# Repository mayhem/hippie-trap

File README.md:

# led-chandelier
LED bottle chandelier built for Nowhere 2015

by Robert Kaye and David Martin

Mock-up
=======

For a render of what we think this might look like a look in the design folder.

Hardware notes
==============

The chandalier made up of about 100 bottles that will have circuit boards with LEDs
inside them. 4 RGD LEDs (WS2812B) connected to an atmega128 will light up each bottle.
Communication happens over a bone simple serial connection, hopefully at 250kbps.
For serial timing and ram reasons, I chose the atmega128 over the attiny84.

The bottles will be connected to 5V power, ground and a communication line. The communication
will be via a line driver that broadcasts the serial signal to each bottle. The RPi can then
send either color information to each bottle or more interestingly send a crude set of instructions
on how to build a color animation. This way the chanelier can work in a centrally coordinated
mode or each bottle carrying out its own program.

.brd and .sch files for Eagle are in hardware folder.

Notes about the circuit
-----------------------

- Regulated 5V power supply in the body of the chandelier
- WS2812B LEDS: http://www.adafruit.com/datasheets/WS2812B.pdf
- MCU: atmega168
- Shottky diodes on the inputs.
- Program via a pogoplug, no actual connector will be on the board.

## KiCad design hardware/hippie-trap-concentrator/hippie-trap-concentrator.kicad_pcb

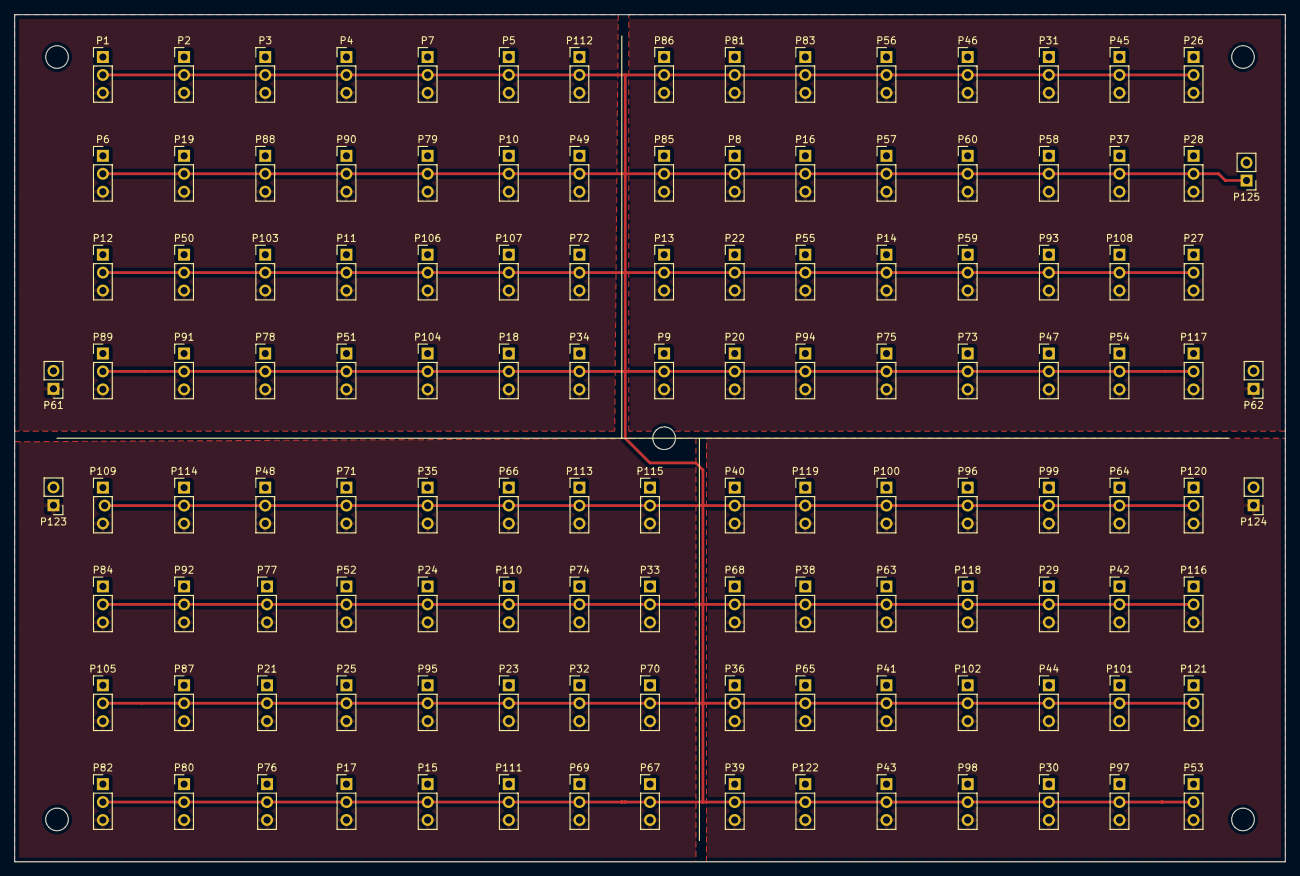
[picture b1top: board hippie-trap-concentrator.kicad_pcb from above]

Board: 2 copper layers, 180.0 x 120.0 mm, 125 parts (0 on the bottom side), 3 nets.

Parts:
P1, P2, P3, P4, P5, P6, P7, P8, P9, P10, P11, P12, P13, P14, P15, P16, P17, P18, P19, P20, P21, P22, P23, P24, P25, P26, P27, P28, P29, P30, P31, P32, P33, P34, P35, P36, P37, P38, P39, P40, P41, P42, P43, P44, P45, P46, P47, P48, P49, P50, P51, P52, P53, P54, P55, P56, P57, P58, P59, P60, P63, P64, P65, P66, P67, P68, P69, P70, P71, P72, P73, P74, P75, P76, P77, P78, P79, P80, P81, P82, P83, P84, P85, P86, P87, P88, P89, P90, P91, P92, P93, P94, P95, P96, P97, P98, P99, P100, P101, P102, P103, P104, P105, P106, P107, P108, P109, P110, P111, P112, P113, P114, P115, P116, P117, P118, P119, P120, P121, P122: CONN_01X03; Pin_Header_Straight_1x03_Pitch2.54mm
P61: PWR1; Pin_Header_Straight_1x02_Pitch2.54mm
P62: PWR2; Pin_Header_Straight_1x02_Pitch2.54mm
P123: PWR3; Pin_Header_Straight_1x02_Pitch2.54mm
P124: PWR4; Pin_Header_Straight_1x02_Pitch2.54mm
P125: RPi; Pin_Header_Straight_1x02_Pitch2.54mm

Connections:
/5V: P1.3, P2.3, P3.3, P4.3, P5.3, P6.3, P7.3, P8.3, P9.3, P10.3, P11.3, P12.3, P13.3, P14.3, P15.3, P16.3, P17.3, P18.3, P19.3, P20.3, P21.3, P22.3, P23.3, P24.3, P25.3, P26.3, P27.3, P28.3, P29.3, P30.3, P31.3, P32.3, P33.3, P34.3, P35.3, P36.3, P37.3, P38.3, P39.3, P40.3, P41.3, P42.3, P43.3, P44.3, P45.3, P46.3, P47.3, P48.3, P49.3, P50.3, P51.3, P52.3, P53.3, P54.3, P55.3, P56.3, P57.3, P58.3, P59.3, P60.3, P61.1, P62.1, P63.3, P64.3, P65.3, P66.3, P67.3, P68.3, P69.3, P70.3, P71.3, P72.3, P73.3, P74.3, P75.3, P76.3, P77.3, P78.3, P79.3, P80.3, P81.3, P82.3, P83.3, P84.3, P85.3, P86.3, P87.3, P88.3, P89.3, P90.3, P91.3, P92.3, P93.3, P94.3, P95.3, P96.3, P97.3, P98.3, P99.3, P100.3, P101.3, P102.3, P103.3, P104.3, P105.3, P106.3, P107.3, P108.3, P109.3, P110.3, P111.3, P112.3, P113.3, P114.3, P115.3, P116.3, P117.3, P118.3, P119.3, P120.3, P121.3, P122.3, P123.1, P124.1
/DATA: P1.2, P2.2, P3.2, P4.2, P5.2, P6.2, P7.2, P8.2, P9.2, P10.2, P11.2, P12.2, P13.2, P14.2, P15.2, P16.2, P17.2, P18.2, P19.2, P20.2, P21.2, P22.2, P23.2, P24.2, P25.2, P26.2, P27.2, P28.2, P29.2, P30.2, P31.2, P32.2, P33.2, P34.2, P35.2, P36.2, P37.2, P38.2, P39.2, P40.2, P41.2, P42.2, P43.2, P44.2, P45.2, P46.2, P47.2, P48.2, P49.2, P50.2, P51.2, P52.2, P53.2, P54.2, P55.2, P56.2, P57.2, P58.2, P59.2, P60.2, P63.2, P64.2, P65.2, P66.2, P67.2, P68.2, P69.2, P70.2, P71.2, P72.2, P73.2, P74.2, P75.2, P76.2, P77.2, P78.2, P79.2, P80.2, P81.2, P82.2, P83.2, P84.2, P85.2, P86.2, P87.2, P88.2, P89.2, P90.2, P91.2, P92.2, P93.2, P94.2, P95.2, P96.2, P97.2, P98.2, P99.2, P100.2, P101.2, P102.2, P103.2, P104.2, P105.2, P106.2, P107.2, P108.2, P109.2, P110.2, P111.2, P112.2, P113.2, P114.2, P115.2, P116.2, P117.2, P118.2, P119.2, P120.2, P121.2, P122.2, P125.1
/GND: P1.1, P2.1, P3.1, P4.1, P5.1, P6.1, P7.1, P8.1, P9.1, P10.1, P11.1, P12.1, P13.1, P14.1, P15.1, P16.1, P17.1, P18.1, P19.1, P20.1, P21.1, P22.1, P23.1, P24.1, P25.1, P26.1, P27.1, P28.1, P29.1, P30.1, P31.1, P32.1, P33.1, P34.1, P35.1, P36.1, P37.1, P38.1, P39.1, P40.1, P41.1, P42.1, P43.1, P44.1, P45.1, P46.1, P47.1, P48.1, P49.1, P50.1, P51.1, P52.1, P53.1, P54.1, P55.1, P56.1, P57.1, P58.1, P59.1, P60.1, P61.2, P62.2, P63.1, P64.1, P65.1, P66.1, P67.1, P68.1, P69.1, P70.1, P71.1, P72.1, P73.1, P74.1, P75.1, P76.1, P77.1, P78.1, P79.1, P80.1, P81.1, P82.1, P83.1, P84.1, P85.1, P86.1, P87.1, P88.1, P89.1, P90.1, P91.1, P92.1, P93.1, P94.1, P95.1, P96.1, P97.1, P98.1, P99.1, P100.1, P101.1, P102.1, P103.1, P104.1, P105.1, P106.1, P107.1, P108.1, P109.1, P110.1, P111.1, P112.1, P113.1, P114.1, P115.1, P116.1, P117.1, P118.1, P119.1, P120.1, P121.1, P122.1, P123.2, P124.2, P125.2

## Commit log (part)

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2015-04-09 Only darkness before this commit
2015-04-09 Added the basic node firmware
2015-04-09 Finished layout and silkscreen work
2015-04-10 test version of a master node
2015-04-10 Brining in the proof of concept RPI code
2015-04-11 Got basic serial comms working
2015-04-11 Basic working node code, updated schematic and layout
2015-04-13 Fixed the orientation of the shottky diodes, improved the layout a bit
2015-04-13 Finished layot and silkscreening. Hopefully ready to go!
2015-04-13 Update README.md
    Adding names.
2015-04-14 Added mounting holes. Might be done now!
2015-04-14 Function generators!
2015-04-14 Increased bulk capacitance (C1) to 47uF.
2015-04-14 Starting with fancy pants music sysnthesis approach to making pretty lights.
2015-04-16 Interim check-in
2015-04-16 Renamed files to be singular
2015-04-16 Added amplitude support and tested sine
2015-04-18 Tools to program node ids
2015-04-18 Added support for ids and packet types and added color array packet type
2015-05-06 Change the yellow to be more orange
2015-05-20 Added code to describe the parameters that need to be sent to the chandelier. Reworked an existing pattern to not use state or an external while loop. I understand functional programming now!! (While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
2015-05-20 Cleanup and simplification.
2015-05-23 Finished implementing and debuggin serializing and reading. Evaluation is next!
2015-05-30 Debugged the generator functions. Verified visually.
2015-05-30 The code works for values |t| < 2000, but it gets inaccurate beyond that. :(
2015-05-31 Implemented sawtooth function
2015-06-01 Interim commit
2015-06-02 Moving things to classes -- interim check-in. Nearly finished with functions.
2015-06-02 Finished implementing the basic functions needed to test the proof of concept. Now I just need to call the functions and generate some output!
2015-06-04 Finished porting source back to C
2015-06-04 Interim check in. Not compiling even. :)
2015-06-06 Seems basic setup works for at least one function.
2015-06-06 Implemented hsb to rgb using integer math
2015-06-06 Finished debugging the rainbow/wobble. Improve generator parameter ordering consistency
2015-06-07 Ported code to aduino and it looks like everything should fit!!!
2015-06-07 2 patterns work correctly!
2015-06-07 2 patterns work, but only one before something gets unhappy.
2015-06-09 Add support for sending random number seeds. Refactor sending of packets
2015-06-09 Remote controlling of patterns now works.
2015-06-09 Finished debugging the ability to load two patterns into ram at once
2015-06-11 Implemented error support with color coding scheme
2015-06-11 Added transition support
2015-06-11 Implemented speed and fixed transitions.
2015-06-11 Some stuff is debugged, but most everything is somewhat broken. :/
2015-06-11 Debugging, but lots of bugs in transitions.
2015-06-12 Started work on addresses
2015-06-13 Refactoring chandelier code a little
2015-06-13 Finished debugging HSV
2015-06-14 The C code now fully behaves in the same way at the python code! \ø/
2015-06-14 Fixed old direct drive mode
2015-06-15 Implemented operators for sources
2015-06-20 Basic text box with styling
2015-06-20 Added submit function, but back-end not implemented yet
2015-06-21 Implemented complementary color source and constant function generator
2015-06-22 another WIP
2015-06-22 partially implemented local functions
2015-06-22 Finished debugging local functions
2015-06-23 Added a plotting function for generators!
2015-06-23 Increase granularity of sin table
2015-06-23 Implemented broadcast classes
2015-06-23 Add reference graphs for the generators
2015-06-23 Implemented a server version of repeat local random number
2015-06-24 Random color sequence is working!
2015-06-24 Don't cast the const value to 8 bit
2015-06-24 Clamp HSV inputs properly, fix a wrong function pointer call
2015-06-24 Allow indefinite debug and command line arg for local not local on dev.py
2015-06-24 Fixed and tested speed setting
2015-06-24 Tested clear next pattern, moved test scripts to tests dir
2015-06-24 Set speed to 100% upon startup
2015-06-25 Implemented the C++ side of timer calibration
2015-06-25 Fix sending entropy to all the nodes
2015-06-26 Added the finished RGB -> HSV function
2015-06-26 Implemented color shift filter
2015-06-26 Added constant random color
2015-06-26 Debugged constant random color
2015-06-26 Debugged color filtering. Still one bug remains in RGB to HSV
2015-06-26 Debugged node id setting and classes
2015-06-26 Debgged complementary colors
2015-06-27 Timing debugged, actual bottles are working fine
2015-06-27 Tuned packet size based on heap/stack inspection
2015-06-27 After tuning max packet size, added a check for exceeding the packet size
2015-06-28 Added RGBSource. Added ability to skip a frame. Properly implemented top level filter.
2015-06-28 Added support for sending position
2015-06-28 implemented a new time calibration routine that works!
2015-06-28 Improved time calibration
2015-06-28 Ditched color filter and implemented simple brightness
2015-06-28 Color shift filter fixes, added fade test
2015-06-28 Change complementary function to use a func as dist
2015-06-28 Change complementary function to use func for dist
2015-06-29 Allow for negative time and fix and made python and c's % consistent
2015-06-29 Changed color to be a src argument for comp color
2015-06-29 Added support for the third source op (for +, -)
2015-06-29 Minor fix on src op
2015-06-29 Finished the XYZ function. Let's hope it works. :)
2015-06-29 First cut at XYZ source. it compiles!
2015-06-29 Debugged the XYZ source.
2015-06-30 Fixed sending positions
2015-06-30 Minor tweaks to programming setup
2015-06-30 Reworked the whole script for progamming nodes
2015-07-01 I hate level shifters. I love atmels. :)
2015-07-01 Implemented live coding!
2015-07-02 Entropy is now 4 bytes and use only three colors at startup
2015-07-04 Committing changes from the desert:
    55ab94309cf93387026938f35b86b5d3a23fd02b 19d6c84e2b0a3d63f62f3f931567741c8993bf1f Robert Kaye <rob@musicbrainz.org> 1435874290 +000 commit: Desert hacking!
    19d6c84e2b0a3d63f62f3f931567741c8993bf1f 57783c7ede4a130361c9ac590669f69f0a9afd72 Robert Kaye <rob@musicbrainz.org> 1435882204 +000 commit: Possibly fix it!
    57783c7ede4a130361c9ac590669f69f0a9afd72 01041ae2d82dbe030008152e4dc76a8f78ba0bd2 Robert Kaye <rob@musicbrainz.org> 1435882509 +000 commit: Fixed the bug!
    Whatever those mean. :)
2015-07-05 Added control end points
2015-07-05 Finished debugging the relay
2015-07-05 Implemented brightness and speed control
2015-08-03 Updated the interface to not use HTTP
2016-01-08 Now the base is even cool!
2016-01-13 Hopefully final versions of the wood cuts for the flower
2016-01-17 Change support for how IDs are assigned
2016-01-17 Added support for local angles
2016-01-17 Finish debugging radial support
2016-01-17 Finished debugging and improving pattern classes.
2016-01-17 Trying to fix GenOp, no luck so far. Will work on that later.
2016-01-19 Fixed reverse pattern for local angle
2016-01-19 It is coming together!
2016-02-03 ORD camp fixes
2017-09-07 Checking nearly complete concentrator
2017-09-10 Start cleanup, and fixup after core function rewrite
2017-09-11 Rewrite complete, square functions work
2017-10-28 Got bootloader hello world working.
2017-10-29 Save before ditching arduino.
2017-10-29 Another interim check in
2017-10-29 It compiles!
2017-10-29 Improve bootloader on and off
2017-10-30 non-arduino codebase seems to be working!
2017-11-01 Interim check in trying to get things sane
2017-11-02 Get a sanity check and off working with the new setup.
2017-11-02 Another interim check-in as the multi-upload features get debugged.
2017-11-02 Calibration improvements
2017-11-02 More bootloader tweaks and debugging
2017-11-03 More tweaks, more debugging. Resets from node work, but still don't enter the bootloader
2017-11-03 Bootloader is getting there, but the node does not reboot into the bootloader.
2017-11-03 Happy with the bootloader so far. I bet I'll find ways it needs improving later.
2017-11-05 add a set_error() function for improved error handling
2017-11-09 Make an error a pattern
2017-11-09 Make the error function a normal pattern
2017-11-10 Messy!
2017-11-10 Found minor problem in packet receiving code. Now CRC checking works correctly.
2018-04-16 Implement more functions, including the critical rainbow function
2018-04-16 Adjustments to bootloader for greater resiliency
2018-04-16 Fix calibrate script
2018-04-17 Started to implement decay, but the code doesn't seem to work. Interim checkin
2018-04-17 Implement setting a single LED
2018-04-17 Minor fixes
2018-04-19 Add panic recovery feature in case bad firmware gets uploaded.
2018-04-19 Adding serial
2018-04-19 Debugging hardening the bootloader
2018-04-20 Program fuses when programming the id
2018-04-22 Finally fixed the fade function
2018-04-22 Increase the panic count
2018-04-23 Add test script for fade pattern
2018-04-23 rename chandelier -> hippietrap
2018-04-23 Port fire and ice to fade
2018-04-23 Simplify more code, remove redundancies, fix fading
2018-04-24 First attempt at a fade out. Not very good, but better than just off
2018-05-09 Refactor to have RPi turn off serial port when not running.
2018-05-12 Fix uploding since new interrupt driven serial io
2018-05-12 use BOD detection
2018-05-12 Toss out the forced bootloader crap for now.
2018-05-12 Use bottle entropy for internal rainbow pattern
2018-05-12 Turn off brightness control it crashed everything again. Now trying forcing to bootloader via the startup sequence
2018-05-13 More debugging for robustness
2018-05-14 Classes have been renamed to groups and seem to work!
2018-05-14 Brightness still doesn't work right. Giving up for now.
2018-05-15 Silly noddling around.
2018-05-26 Add fade to random color support
2018-05-28 Added geometry class to helping with common bottle enumerations. Implemented some sweet sweep patterns
2018-06-10 Software changes for new SSR power control
2018-06-11 The clock is starting to function
2018-06-11 The clock is working
2018-09-08 Clear screen
2018-09-08 Test new sin function
2018-09-09 brightness still not fully fixed. sigh.
2018-09-09 Minor tweak
2018-09-09 Major cleanup and standardization of existing patterns -- next step automating them!
2018-09-09 Grduate some patterns
2018-09-09 Refactor to allow dynamic loading of patterns
2018-09-09 move sin things along, but too stoned to solve this now. :)
2018-09-09 Fix swappies, disable sparkle
2018-09-10 Fixing up patterns that relied on being two rings.
2018-09-11 More robustness bits, removing debug
2018-09-11 Added delays and better error checking to node programmer
2018-09-11 Improving patterns, promising!
2018-09-15 More tweaks trying to make patterns look good with 4 levels.
2018-09-18 Finished debugging the new brightness code. Took forever!
2018-09-19 Fix fade patterns to ms, not ticks for more predictable behaviour
2019-01-24 Minor tweaks to patterns
2019-01-25 Connect the hippie trap to MQTTT
2019-01-25 Finished migrating all the patterns.
2019-01-25 Fixe fire ice circles. A little less circley now, but soo good
2019-01-27 Add a left to right sweep transition
2019-01-27 Add a lateral sweep transition
2019-02-01 Somehow the sin function made the brightness code crash. WTF?
2019-06-26 First cut at py3 version. Loads of bugs!
2019-06-27 Start on MQTT clean up
2019-06-27 Fix firmware sending
2019-06-27 Finish reworking core enable/disable power on/off code for good mqtt support
2019-07-04 Sweep in reverse
2019-07-04 Tweaks on the outward pattern
2021-01-03 Fix pyhon3 uploading and other improvements
2021-01-03 Improve sweeping patterns
2021-01-04 Add new checker sweep pattern. Not fully finished, but a nice start
2022-07-28 Implement brightness up/down
2022-07-28 Add next and repeat pattern functionality
2023-05-10 Add hue shift to set color function
2023-12-26 First stab at night time mdoe
2023-12-26 Check in latest improvements before OS upgrade
2023-12-26 Interim check-in after upgrading OS and a few refactor changes
2023-12-26 Make the scheme a feature of the hippie trap
